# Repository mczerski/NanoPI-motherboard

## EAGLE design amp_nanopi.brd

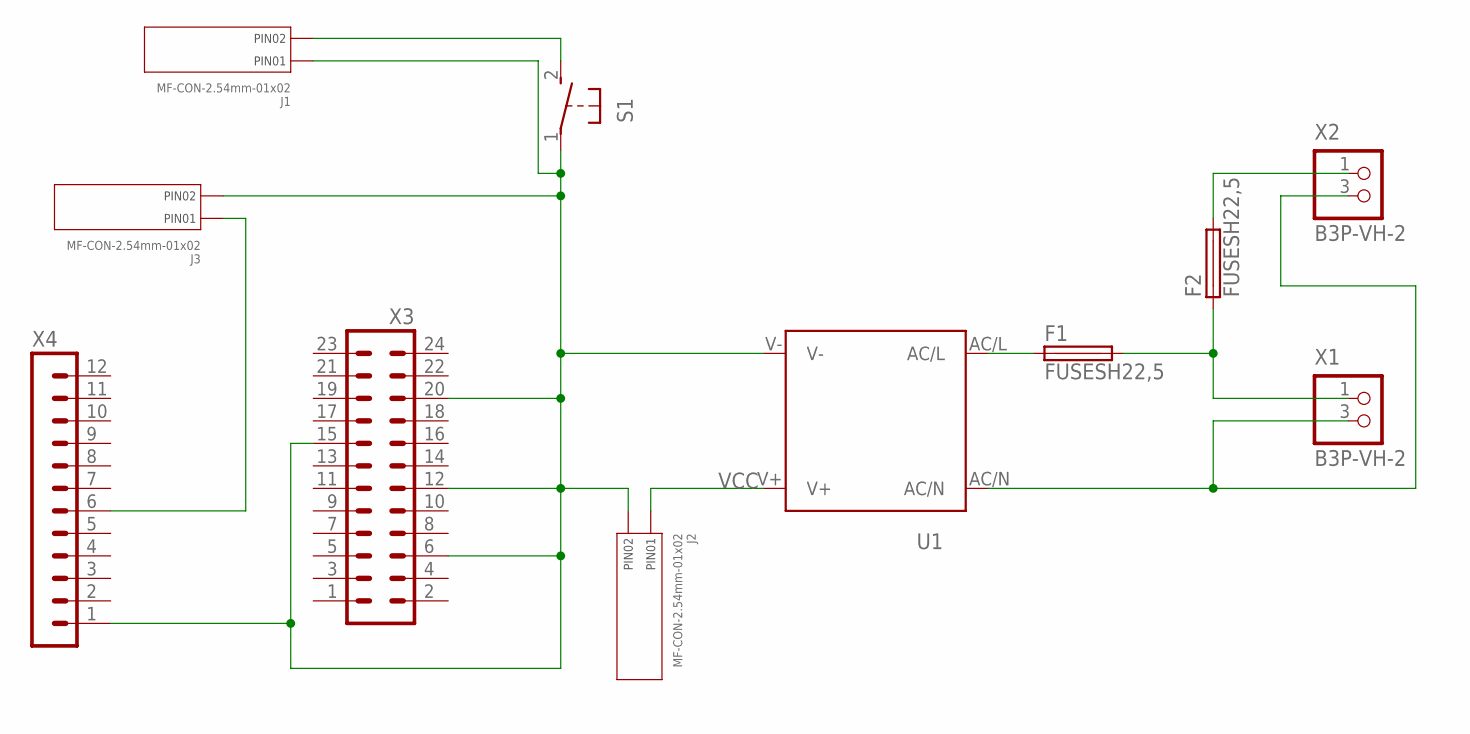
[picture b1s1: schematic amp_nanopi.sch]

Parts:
F1, F2: FUSESH22,5; SH22,5
J1, J2, J3: MF-CON-2.54mm-01x02; PTH_2.54MM_01X02
S1: 31-XX; B3F-31XX
U1: IRM_05/10
X1, X2: B3P-VH-2
X3: MA12-2
X4: MA12-1

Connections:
GND: J1.P$1 (PIN1), J2.P$2 (PIN2), J3.P$2 (PIN2), S1.1, U1.V-, X3.6, X3.12, X3.15, X3.20, X4.1
unnamed: J3.P$1 (PIN1), X4.6
unnamed: F2.2, X2.1
unnamed: F1.2, F2.1, X1.1
unnamed: F1.1, U1.AC/L
unnamed: U1.AC/N, X1.3 (2), X2.3 (2)
PWR: J1.P$2 (PIN2), S1.2 (S)
VCC: J2.P$1 (PIN1), U1.V+

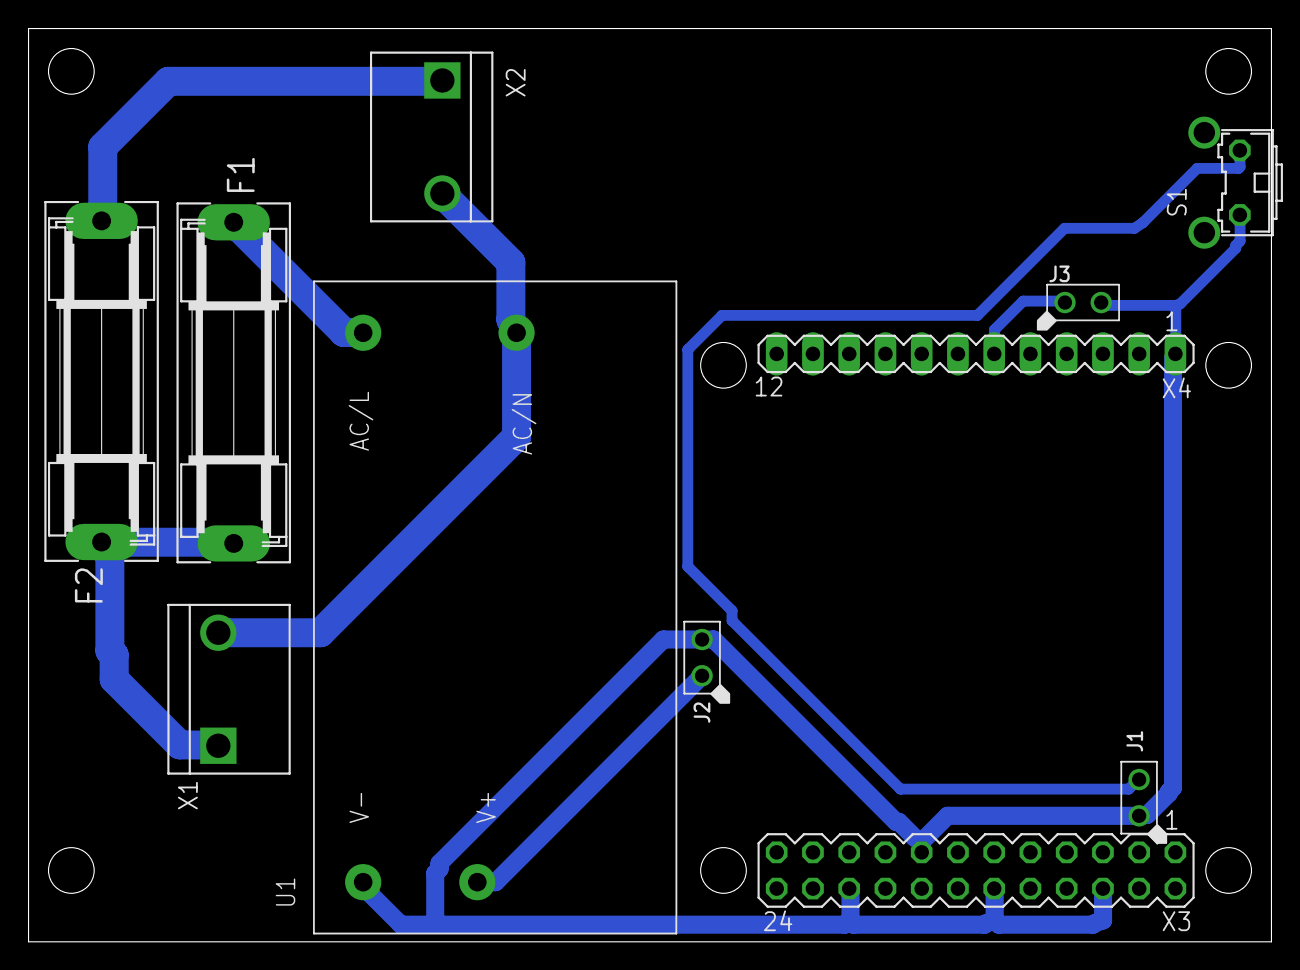
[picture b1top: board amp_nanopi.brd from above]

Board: 2 copper layers, 87.1 x 64.0 mm, 11 parts (0 on the bottom side), 8 nets.

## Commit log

2017-04-28 pierwszy commit
2017-04-29 dostosowanie do nowego projektu safe_pi_shutdown
2017-05-21 poprawka zlacza zasilania tak aby nie kolidowalo z zasilaczem
2017-06-17 dodatkowy otwór dla nanopi
2017-06-18 przygotowanie do wyslania do pcbs.io
